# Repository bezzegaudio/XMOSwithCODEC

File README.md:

XMOS XU316 based prototype board with audio CODEC. NOTE: THE DESIGN HAS NOT BEEN VERIFIED AS IN BUILT YET

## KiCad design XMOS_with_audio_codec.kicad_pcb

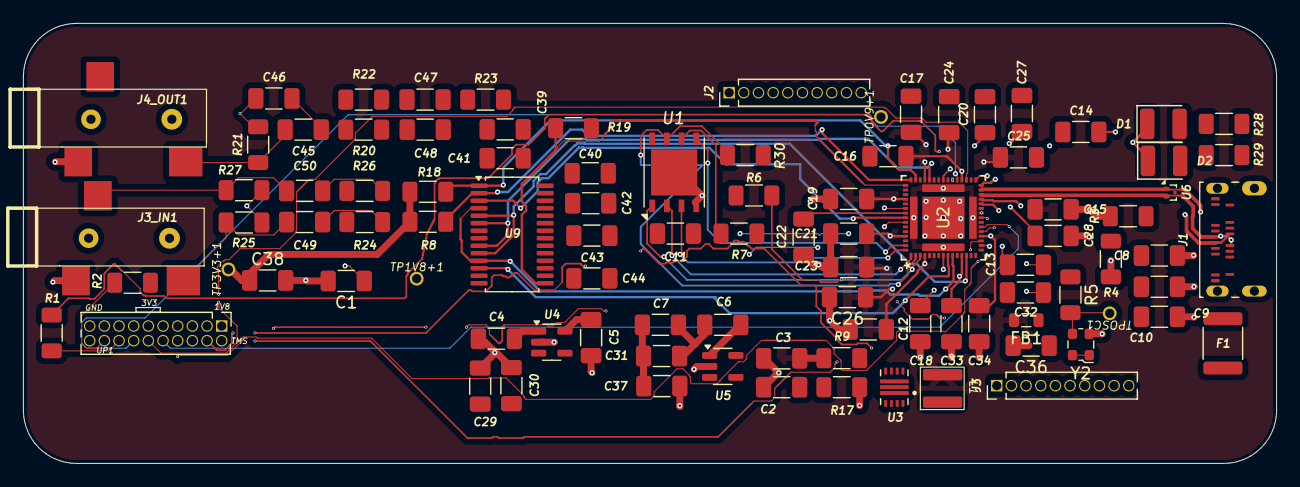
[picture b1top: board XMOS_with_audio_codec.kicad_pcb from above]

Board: 4 copper layers, 108.5 x 38.1 mm, 95 parts (0 on the bottom side), 73 nets.

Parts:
C1, C11, C12, C13, C14, C15, C16, C17, C18, C19, C20, C21, C22, C23, C24, C25, C26, C27, C28, C33, C34, C36, C38, C39, C40, C43: 100n; C_1206_3216Metric_Pad1.33x1.80mm_HandSolder
C2: 10uF XR7; C_1206_3216Metric_Pad1.33x1.80mm_HandSolder
C3: 22u; C_1206_3216Metric_Pad1.33x1.80mm_HandSolder
C4, C5, C6, C7: 4.7u CER X5R/X7R; C_1206_3216Metric_Pad1.33x1.80mm_HandSolder
C8, C45, C47: 10uF; C_1206_3216Metric_Pad1.33x1.80mm_HandSolder
C9: 100n ceramic; C_1206_3216Metric_Pad1.33x1.80mm_HandSolder
C10, C29, C37, C41, C42, C44: 10u; C_1206_3216Metric_Pad1.33x1.80mm_HandSolder
C30, C31: 100n near XU316; C_1206_3216Metric_Pad1.33x1.80mm_HandSolder
C32: 1u X7R; C_1206_3216Metric_Pad1.33x1.80mm_HandSolder
C46, C48: 3.3n; C_1206_3216Metric_Pad1.33x1.80mm_HandSolder
C49, C50: 4.7uF; C_1206_3216Metric_Pad1.33x1.80mm_HandSolder
D1: POWER; LED_1210_3225Metric
D2: BLINKY_BLUE; LED_1210_3225Metric
F1: MF-MSMF050-2; Fuse_1812_4532Metric
FB1: 81-BLM21BD601SZ1D; L_0805_2012Metric
J1: USB_C_Receptacle_USB2.0_14P; USB_C_Receptacle_Amphenol_124019772112A
J2, J3: Conn_01x11_Pin; PinHeader_1x10_P1.27mm_Vertical
J3_IN1, J4_OUT1: SJ-3523-SMT-TR; CUI_SJ-3523-SMT-TR
L1: 1uH Coilcraft XAL4020-102MEC; Coilcraft XAL4020-102MEC
R1, R2: 43; R_1206_3216Metric_Pad1.30x1.75mm_HandSolder
R3, R4: 5.1K; R_1206_3216Metric_Pad1.30x1.75mm_HandSolder
R5, R7: 22; R_1206_3216Metric_Pad1.30x1.75mm_HandSolder
R6: 47k; R_1206_3216Metric_Pad1.30x1.75mm_HandSolder
R8, R18: 4.7k; R_1206_3216Metric_Pad1.30x1.75mm_HandSolder
R9: 28.7K 1%; R_1206_3216Metric_Pad1.30x1.75mm_HandSolder
R17: 100K 1%; R_1206_3216Metric_Pad1.30x1.75mm_HandSolder
R19, R30: 10k; R_1206_3216Metric_Pad1.30x1.75mm_HandSolder
R20, R22, R24, R26, R29: 1k; R_1206_3216Metric_Pad1.30x1.75mm_HandSolder
R21, R23, R25, R27: 100k; R_1206_3216Metric_Pad1.30x1.75mm_HandSolder
R28: 2.2k; R_1206_3216Metric_Pad1.30x1.75mm_HandSolder
TP0V9+1, TP1V8+1, TP3V3+1: TestPoint; TestPoint XMOS
TPOSC1: TestPoint; TestPoint XMOS
U1: AT25FF321A-MHN-T; DFN-8-1EP_6x5mm_P1.27mm_EP4x4mm
U2: XU316-1024-QF60B; QFN_F60B-C24_XMO
U3: TPS62135RGXR; VREG_TPS621361RGXR
U4: TLV75733PDBV; SOT-23-5
U5: TLV75718PDBV; SOT-23-5
U6: TPD2EUSB30; Texas_DRT-3
U8: JTAG Header; PinHeader_2x10_P1.27mm_Vertical
U9: PCM3060; TSSOP-28_4.4x9.7mm_P0.65mm
Y2: ECS-2520MV-24MHz; Oscillator_SMD_ECS_2520MV-xxx-xx-4Pin_2.5x2.0mm

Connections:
0V9: C3.1, C12.1, C15.1, C16.1, C17.1, C19.1, C21.1, C23.1, C24.1, C25.1, C26.1, C33.1, C34.1, FB1.2, L1.2, R9.1, TP0V9+1.1, U2.4 (VDD), U2.12 (VDD), U2.19 (VDD), U2.27 (VDD), U2.34 (VDD), U2.42 (VDD), U2.49 (VDD), U2.57 (VDD), U2.61 (VDD), U2.62 (VDD), U2.63 (VDD), U2.64 (VDD), U3.6 (VOS)
1V8: C1.1, C7.1, C13.1, C14.1, C27.1, C31.1, C36.1, C37.1, TP1V8+1.1, U2.17 (VDDBO18), U2.26 (VDDIOB18), U2.31 (USB_VDD18), U5.5 (OUT), U8.1 (VREF_JTAG), Y2.1 (Tri-State), Y2.4 (VDD)
3V3: C5.1, C11.1, C18.1, C20.1, C22.1, C28.1, C29.1, C30.1, C38.1, C39.2, C41.2, J3.10, R6.1, R8.1, R18.1, R19.2, R30.2, TP3V3+1.1, U1.8 (VCC), U2.8 (VDDIOL), U2.30 (USB_VDD33), U2.38 (VDDIOR), U2.52 (VDDIOT), U4.5 (OUT), U8.11 (VREF_LINK), U9.7 (V_{DD})
5V: C2.1, C4.1, C6.1, C9.1, C10.1, C40.1, C42.1, F1.2, J3.9, R28.1, U3.1 (VIN), U3.8 (EN), U3.10 (MODE), U4.1 (IN), U4.3 (EN), U5.1 (IN), U5.3 (EN), U9.24 (V_{CC})
CS: R6.2, U1.1 (CSN), U2.3 (X0D01)
D+: J1.A6 (D+), J1.B6 (D+), U2.29 (USB_DP), U6.1 (D+)
D-: J1.A7 (D-), J1.B7 (D-), U2.28 (USB_DM), U6.2 (D-)
GND: C1.2, C2.2, C3.2, C4.2, C5.2, C6.2, C7.2, C8.1, C9.2, C10.2, C11.2, C12.2, C13.2, C14.2, C15.2, C16.2, C17.2, C18.2, C19.2, C20.2, C21.2, C22.2, C23.2, C24.2, C25.2, C26.2, C27.2, C28.2, C29.2, C30.2, C31.2, C32.2, C33.2, C34.2, C36.2, C37.2, C38.2, C39.1, C40.2, C41.1, C42.2, C43.2, C44.2, C46.1, C48.1, D1.1 (K), D2.1 (K), J2.10, J3_IN1.1 (SLEEVE), J4_OUT1.1 (SLEEVE), R3.2, R4.2, R17.2, R21.2, R23.2, R25.1, R27.1, U1.4 (VSS), U1.9 (PAD), U2.65 (VSS), U3.3 (GND), U3.11 (VSEL), U4.2 (GND), U5.2 (GND), U6.3 (GND), U8.3 (GND), U8.5 (GND), U8.7 (GND), U8.9 (GND), U8.13 (GND), U8.15 (GND), U8.17 (GND), U8.19 (GND), U9.8 (DGND), U9.16 (SGND), U9.22 (AGND2), U9.23 (AGND1), U9.27 (~MS/AD/IFMD), U9.28 (MODE), Y2.2 (GND)
HLD_RST_IO3: R30.1, U1.7 (~HOLD/~RESET/IO3), U2.2 (X0D07)
I2C_SCL: R18.2, U2.44 (X0D37), U9.1 (MC/SCL/FMT)
I2C_SDA: R8.2, U2.45 (X0D38), U9.2 (MD/SDA/DEMP)
I2S_ADC_DATA: U2.53 (X1D34), U9.3 (DOUT)
I2S_BCLK: U2.13 (X1D10), U9.5 (BCK1), U9.10 (BCK2)
I2S_DAC_DATA: U2.9 (X1D00), U9.12 (DIN)
I2S_MCLK: U2.41 (X0D35), U9.6 (SCKI1), U9.9 (SCKI2)
I2S_RCLK: U2.10 (X0D01), U9.4 (LRCK1), U9.11 (LRCK2)
I2S_RST: R19.1, U2.46 (X0D40), U9.15 (~RST)
unnamed: C8.2, F1.1, J1.A4 (VBUS), J1.A9 (VBUS), J1.B4 (VBUS), J1.B9 (VBUS)
unnamed: C45.1, C46.2, R20.1
unnamed: C47.1, C48.2, R22.1
unnamed: C49.2, R24.2
unnamed: C50.2, R26.2
unnamed: D1.2 (A), R28.2
unnamed: D2.2 (A), R29.2
unnamed: J1.A5 (CC1), R3.1
unnamed: J1.B5 (CC2), R4.1
unnamed: J1.A1 (GND), J1.A12 (GND), J1.B1 (GND), J1.B12 (GND), J1.S1 (SHIELD)
unnamed: C50.1, J3_IN1.3 (RING), R27.2
unnamed: C49.1, J3_IN1.2 (TIP), R25.2
unnamed: C47.2, J4_OUT1.3 (RING), R23.1
unnamed: C45.2, J4_OUT1.2 (TIP), R21.1
unnamed: R7.1, U2.5 (X0D10)
unnamed: R5.1, U2.16 (XIN)
unnamed: C32.1, FB1.1, U2.22 (PLL_AVDD)
unnamed: R9.2, R17.1, U3.5 (FB)
unnamed: L1.1, U3.2 (SW)
unnamed: C43.1, C44.1, U9.21 (V_{COM})
unnamed: R24.1, U9.25 (V_{IN}L)
unnamed: R26.1, U9.26 (V_{IN}R)
unnamed: R20.2, U9.20 (V_{OUT}L+)
unnamed: R22.2, U9.18 (V_{OUT}R+)
OSC: R5.2, TPOSC1.1, Y2.3 (OUT)
RESET: J3.8, U2.21 (RST_N), U8.10 (RST_N)
SCLK: R7.2, U1.6 (SCLK)
SI_IO0: U1.5 (SI/IO0), U2.59 (X0D04)
SI_IO1: U1.2 (SO/IO1), U2.1 (X0D05)
WP_IO2: U1.3 (~WP/IO2), U2.60 (X0D06)
X0D00: J2.1, U2.6 (X0D00)
X0D11: J2.2, U2.7 (X0D11)
X0D29: J2.3, U2.40 (X0D29)
X0D30: J2.4, U2.54 (X0D30)
X0D31: J2.5, U2.55 (X0D31)
X0D32: J2.6, U2.56 (X0D32)
X0D33: J2.7, U2.58 (X0D33)
X0D36: J2.8, U2.43 (X0D36)
X0D39: J2.9, U2.47 (X0D39)
X0D41: J3.1, U2.50 (X0D41)
X0D42: J3.2, U2.48 (X0D42)
X0D43: J3.3, R29.1, U2.51 (X0D43)
X1D09: J3.4, U2.11 (X0D09)
X1D11: J3.5, U2.14 (X1D11)
X1D13: J3.6, U2.32 (X1D13)
X1D18: R1.1, U2.36 (X1D18)
X1D19: R2.1, U2.37 (X1D19)
X1D22: J3.7, U2.39 (X1D22)
XL_DN0: U2.35 (X1D17), U8.14 (XL_DN0)
XL_DN1: U2.33 (X1D16), U8.12 (XL_DN1)
XL_UP0: R1.2, U8.16 (XL_UP0)
XL_UP1: R2.2, U8.18 (XL_UP1)
xSYS2_TCK: U2.24 (TCK), U8.4 (TCK)
xSYS2_TDI: U2.18 (TDI), U8.8 (TDI)
xSYS2_TDO: U2.20 (TDO), U8.6 (TDO)
xSYS2_TMS: U2.23 (TMS), U8.2 (TMS)

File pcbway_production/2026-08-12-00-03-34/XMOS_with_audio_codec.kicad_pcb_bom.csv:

Designator,Quantity,Value,Footprint,Package,MPN,DNP,Mount_Type,Description,Sim.Pins,MF,Description_1,Price,Check_prices,SnapEDA_Link,MP,Availability,MANUFACTURER
"C1, C11, C12, C13, C14, C15, C16, C17, C18, C19, C20, C21, C22, C23, C24, C25, C26, C27, C28, C33, C34, C36, C38, C39, C40, C43",26,100n,C_1206_3216Metric_Pad1.33x1.80mm_HandSolder,,,,smt,Unpolarized capacitor,,,,,,,,,
"C10, C29, C37, C41, C42, C44",6,10u,C_1206_3216Metric_Pad1.33x1.80mm_HandSolder,,,,smt,Unpolarized capacitor,,,,,,,,,
C2,1,10uF XR7,C_1206_3216Metric_Pad1.33x1.80mm_HandSolder,,,,smt,Unpolarized capacitor,,,,,,,,,
C3,1,22u,C_1206_3216Metric_Pad1.33x1.80mm_HandSolder,,,,smt,Unpolarized capacitor,,,,,,,,,
"C30, C31",2,100n near XU316,C_1206_3216Metric_Pad1.33x1.80mm_HandSolder,,,,smt,Unpolarized capacitor,,,,,,,,,
C32,1,1u X7R,C_1206_3216Metric_Pad1.33x1.80mm_HandSolder,,,,smt,Unpolarized capacitor,,,,,,,,,
"C4, C5, C6, C7",4,4.7u CER X5R/X7R,C_1206_3216Metric_Pad1.33x1.80mm_HandSolder,,,,smt,Unpolarized capacitor,,,,,,,,,
"C45, C47, C8",3,10uF,C_1206_3216Metric_Pad1.33x1.80mm_HandSolder,,,,smt,"[C45,C47]Unpolarized capacitor, small symbol; [C8]Unpolarized capacitor",,,,,,,,,
"C46, C48",2,3.3n,C_1206_3216Metric_Pad1.33x1.80mm_HandSolder,,,,smt,"Unpolarized capacitor, small symbol",,,,,,,,,
"C49, C50",2,4.7uF,C_1206_3216Metric_Pad1.33x1.80mm_HandSolder,,,,smt,"Unpolarized capacitor, small symbol",,,,,,,,,
C9,1,100n ceramic,C_1206_3216Metric_Pad1.33x1.80mm_HandSolder,,,,smt,Unpolarized capacitor,,,,,,,,,
D1,1,POWER,LED_1210_3225Metric,,,,smt,Light emitting diode,1=K 2=A,,,,,,,,
D2,1,BLINKY_BLUE,LED_1210_3225Metric,,,,smt,Light emitting diode,1=K 2=A,,,,,,,,
F1,1,MF-MSMF050-2,Fuse_1812_4532Metric,,,,smt,"Resettable fuse, polymeric positive temperature coefficient",,,,,,,,,
FB1,1,81-BLM21BD601SZ1D,L_0805_2012Metric,,,,smt,Ferrite bead,,,,,,,,,
J1,1,USB_C_Receptacle_USB2.0_14P,USB_C_Receptacle_Amphenol_124019772112A,,,,smt,USB 2.0-only 14P Type-C Receptacle connector,,,,,,,,,
"J2, J3",2,Conn_01x11_Pin,PinHeader_1x10_P1.27mm_Vertical,,,,tht,"Generic connector, single row, 01x10, script generated (kicad-library-utils/schlib/autogen/connector/)",,,,,,,,,
"J3_IN1, J4_OUT1",2,SJ-3523-SMT-TR,CUI_SJ-3523-SMT-TR,None,,,smt,,,Same Sky,"3.5 mm, Stereo, Right Angle, Surface Mount (SMT), 3 Conductors, 0 Internal Switches, Audio Jack Connector",None,https://www.snapeda.com/parts/SJ-3523-SMT-TR/Same+Sky/view-p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,https://www.snapeda.com/parts/SJ-3523-SMT-TR/Same+Sky/view-p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,SJ-3523-SMT-TR,In Stock,CUI Inc
L1,1,1uH Coilcraft XAL4020-102MEC,Coilcraft XAL4020-102MEC,,,,smt,"Inductor, small symbol",,,,,,,,,
"R1, R2",2,43,R_1206_3216Metric_Pad1.30x1.75mm_HandSolder,,,,smt,Resistor,,,,,,,,,
R17,1,100K 1%,R_1206_3216Metric_Pad1.30x1.75mm_HandSolder,,,,smt,Resistor,,,,,,,,,
"R18, R8",2,4.7k,R_1206_3216Metric_Pad1.30x1.75mm_HandSolder,,,,smt,Resistor,,,,,,,,,
"R19, R30",2,10k,R_1206_3216Metric_Pad1.30x1.75mm_HandSolder,,,,smt,Resistor,,,,,,,,,
"R20, R22, R24, R26, R29",5,1k,R_1206_3216Metric_Pad1.30x1.75mm_HandSolder,,,,smt,Resistor,,,,,,,,,
"R21, R23, R25, R27",4,100k,R_1206_3216Metric_Pad1.30x1.75mm_HandSolder,,,,smt,Resistor,,,,,,,,,
R28,1,2.2k,R_1206_3216Metric_Pad1.30x1.75mm_HandSolder,,,,smt,Resistor,,,,,,,,,
"R3, R4",2,5.1K,R_1206_3216Metric_Pad1.30x1.75mm_HandSolder,,,,smt,Resistor,,,,,,,,,
"R5, R7",2,22,R_1206_3216Metric_Pad1.30x1.75mm_HandSolder,,,,smt,Resistor,,,,,,,,,
R6,1,47k,R_1206_3216Metric_Pad1.30x1.75mm_HandSolder,,,,smt,Resistor,,,,,,,,,
R9,1,28.7K 1%,R_1206_3216Metric_Pad1.30x1.75mm_HandSolder,,,,smt,Resistor,,,,,,,,,
U1,1,AT25FF321A-MHN-T,DFN-8-1EP_6x5mm_P1.27mm_EP4x4mm,,,,smt,"3.0V, Standard/Dual/Quad Serial Flash, WSON-8",,,,,,,,,
U2,1,XU316-1024-QF60B,QFN_F60B-C24_XMO,,,,smt,XMOS,,,,,,,,,
U3,1,TPS62135RGXR,VREG_TPS621361RGXR,,,,smt,,,,,,,,,,
U4,1,TLV75733PDBV,SOT-23-5,,,,smt,"1A Low IQ Small Size Low Dropout Voltage Regulator, Fixed Output 3.3V, SOT-23-5",,,,,,,,,
U5,1,TLV75718PDBV,SOT-23-5,,,,smt,"1A Low IQ Small Size Low Dropout Voltage Regulator, Fixed Output 1.8V, SOT-23-5",,,,,,,,,
U6,1,TPD2EUSB30,Texas_DRT-3,,,,smt,"2-Channel ESD Protection for Super-Speed USB 3.0 Interface, DRT-3",,,,,,,,,
U8,1,JTAG Header,PinHeader_2x10_P1.27mm_Vertical,,,,tht,,,,,,,,,,
U9,1,PCM3060,TSSOP-28_4.4x9.7mm_P0.65mm,,,,smt,"24-bit Asynchronous Stereo Audio Codec with 96/192kHz sampling rate, TSSOP-28",,,,,,,,,
Y2,1,ECS-2520MV-24MHz,Oscillator_SMD_ECS_2520MV-xxx-xx-4Pin_2.5x2.0mm,,,,smt,"HCMOS Crystal Clock Oscillator, 2.5x2.0 mm SMD",,,,,,,,,
